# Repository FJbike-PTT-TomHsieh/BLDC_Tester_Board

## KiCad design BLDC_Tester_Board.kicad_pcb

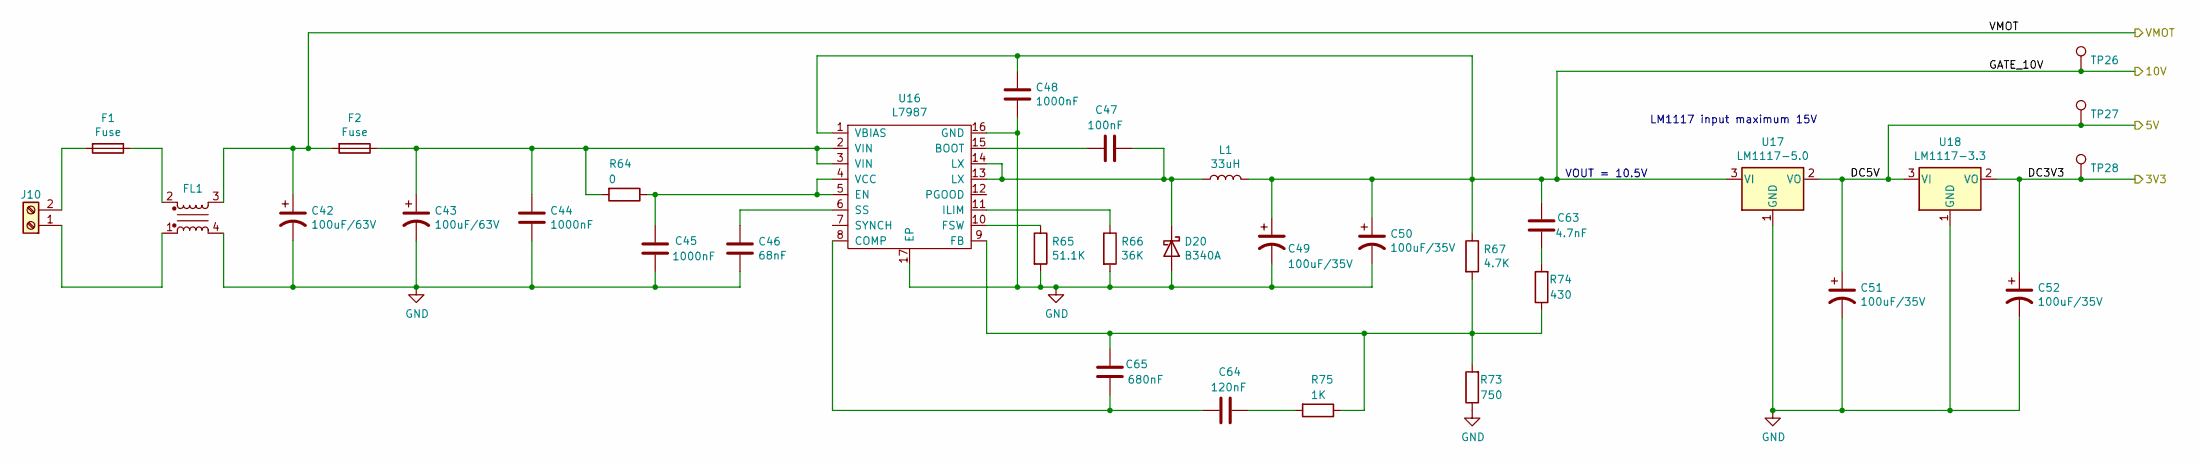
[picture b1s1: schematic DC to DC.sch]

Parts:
C42, C43: 100uF/63V; CP_Radial_D12.5mm_P5.00mm
C44, C45, C48: 1000nF; C_0603_1608Metric_Pad1.08x0.95mm_HandSolder
C46: 68nF; C_0603_1608Metric_Pad1.08x0.95mm_HandSolder
C47: 100nF; C_0603_1608Metric_Pad1.08x0.95mm_HandSolder
C49, C50, C51, C52: 100uF/35V; CP_Radial_D8.0mm_P3.50mm
C63: 4.7nF; C_0603_1608Metric_Pad1.08x0.95mm_HandSolder
C64: 120nF; C_0603_1608Metric_Pad1.08x0.95mm_HandSolder
C65: 680nF; C_0603_1608Metric_Pad1.08x0.95mm_HandSolder
D20: B340A; D_SMA_Handsoldering
F1: Fuse; Fuseholder_Cylinder-5x20mm_Stelvio-Kontek_PTF78_Horizontal_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
F2: Fuse; Fuse_1206_3216Metric_Pad1.42x1.75mm_HandSolder
FL1: EMI_Filter_LL_1423; Choke_Schaffner_RN242-04-18.0x31.0mm
J10: Screw_Terminal_01x02; TerminalBlock_Altech_AK300-2_P5.00mm
L1: 33uH; L_7.3x7.3_H4.5
R64: 0; R_0603_1608Metric_Pad0.98x0.95mm_HandSolder
R65: 51.1K; R_0603_1608Metric_Pad0.98x0.95mm_HandSolder
R66: 36K; R_0603_1608Metric_Pad0.98x0.95mm_HandSolder
R67: 4.7K; R_0603_1608Metric_Pad0.98x0.95mm_HandSolder
R73: 750; R_0603_1608Metric_Pad0.98x0.95mm_HandSolder
R74: 430; R_0603_1608Metric_Pad0.98x0.95mm_HandSolder
R75: 1K; R_0603_1608Metric_Pad0.98x0.95mm_HandSolder
TP26, TP27, TP28: TestPoint; TestPoint_Loop_D2.54mm_Drill1.5mm_Beaded
U16: L7987; HTSSOP-16-1EP_4.4x5mm_P0.65mm_EP3x3mm
U17: LM1117-5.0; SOT-223-3_TabPin2
U18: LM1117-3.3; SOT-223-3_TabPin2

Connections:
/DC to DC/3V3: C52.1, TP28.1, U18.2 (VO); also elsewhere on the board
/DC to DC/5V: C51.1, TP27.1, U17.2 (VO), U18.3 (VI); also elsewhere on the board
/DC to DC/10V: C48.1, C49.1, C50.1, C63.2, L1.2, R67.1, TP26.1, U16.1 (VBIAS), U17.3 (VI); also elsewhere on the board
/DC to DC/VMOT: C42.1, F2.2, FL1.3; also elsewhere on the board
GND: C42.2, C43.2, C44.2, C45.1, C46.2, C48.2, C49.2, C50.2, C51.2, C52.2, D20.2 (A), FL1.4, R65.2, R66.2, R73.1, U16.16 (GND), U16.17 (EP), U17.1 (GND), U18.1 (GND); also elsewhere on the board
unnamed: C43.1, C44.1, F2.1, R64.2, U16.2 (VIN), U16.3 (VIN)
unnamed: C45.2, R64.1, U16.4 (VCC), U16.5 (EN)
unnamed: C46.1, U16.6 (SS)
unnamed: C47.1, D20.1 (K), L1.1, U16.13 (LX), U16.14 (LX)
unnamed: C47.2, U16.15 (BOOT)
unnamed: C63.1, R74.2
unnamed: C64.1, R75.2
unnamed: C64.2, C65.1, U16.8 (COMP)
unnamed: C65.2, R67.2, R73.2, R74.1, R75.1, U16.9 (FB)
unnamed: F1.1, FL1.2
unnamed: F1.2, J10.2
unnamed: FL1.1, J10.1
unnamed: R65.1, U16.10 (FSW)
unnamed: R66.1, U16.11 (ILIM)

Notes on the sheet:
VOUT = 10.5V
LM1117 input maximum 15V

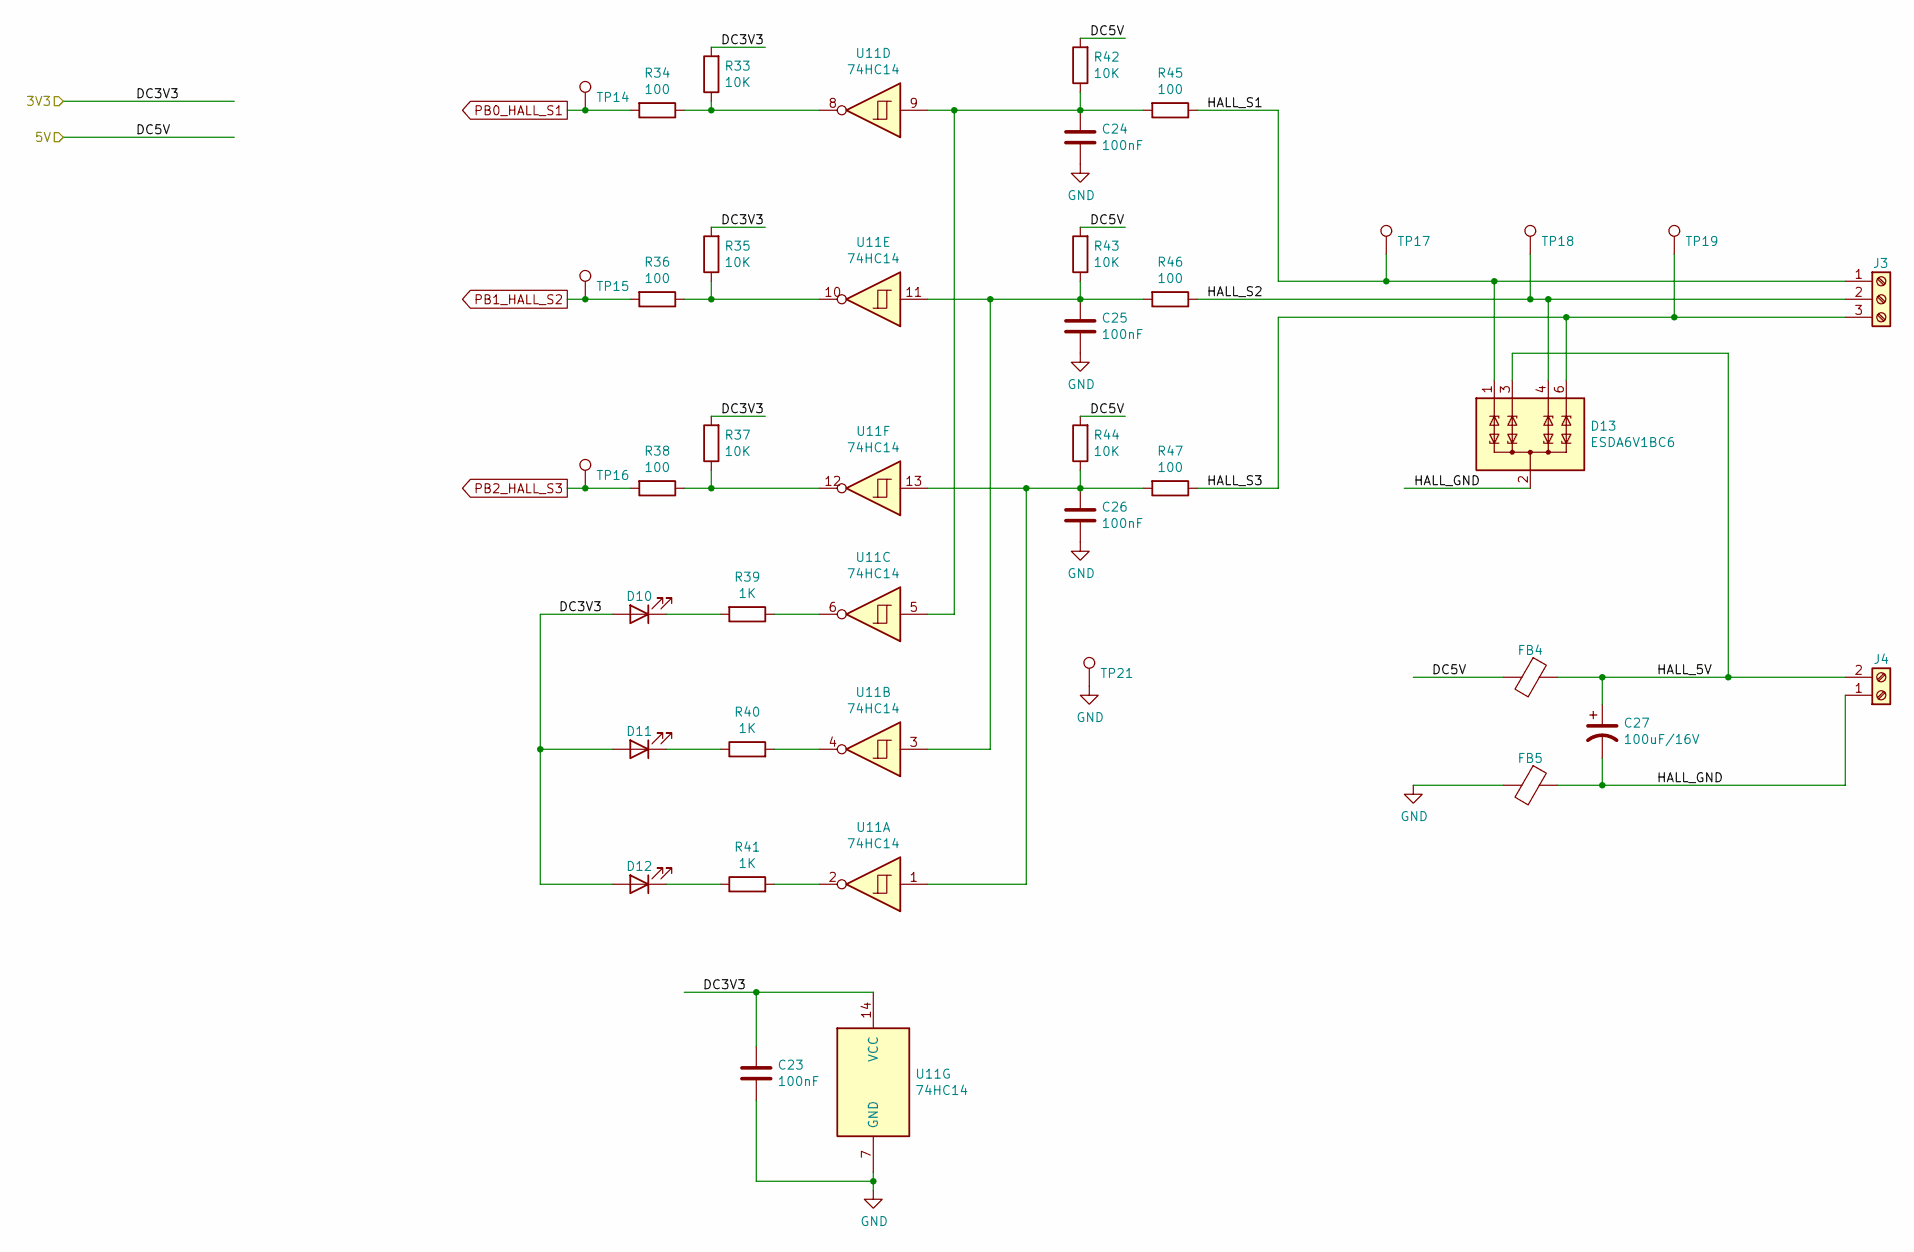
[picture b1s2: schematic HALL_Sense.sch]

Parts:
C23, C24, C25, C26: 100nF; C_0603_1608Metric_Pad1.08x0.95mm_HandSolder
C27: 100uF/16V; CP_Radial_D8.0mm_P3.50mm
D10: PESD5V0L4UG; LED_D3.0mm
D11, D12: LED; LED_D3.0mm
D13: ESDA6V1BC6; SOT-23-6_Handsoldering
FB4, FB5: Ferrite_Bead; R_0603_1608Metric_Pad0.98x0.95mm_HandSolder
J3: Screw_Terminal_01x03; TerminalBlock_4Ucon_1x03_P3.50mm_Horizontal
J4: Screw_Terminal_01x02; TerminalBlock_4Ucon_1x02_P3.50mm_Horizontal
R33, R35, R37, R42, R43, R44: 10K; R_0603_1608Metric_Pad0.98x0.95mm_HandSolder
R34, R36, R38, R45, R46, R47: 100; R_0603_1608Metric_Pad0.98x0.95mm_HandSolder
R39, R40, R41: 1K; R_0603_1608Metric_Pad0.98x0.95mm_HandSolder
TP14, TP15, TP16, TP17, TP18, TP19, TP21: TestPoint; TestPoint_Loop_D2.54mm_Drill1.5mm_Beaded
U11: 74HC14; SO-14_3.9x8.65mm_P1.27mm

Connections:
/DC to DC/3V3: C23.1, D10.2 (A), D11.2 (A), D12.2 (A), R33.2, R35.2, R37.2, U11.14 (VCC); also elsewhere on the board
/DC to DC/5V: FB4.2, R42.2, R43.2, R44.2; also elsewhere on the board
/HALL_Sense/HALL_5V: C27.1, D13.3 (TVS2), FB4.1, J4.2
/HALL_Sense/HALL_GND: C27.2, D13.2 (COM), D13.5 (COM), FB5.1, J4.1
/HALL_Sense/HALL_S1: D13.1 (TVS1), J3.1, R45.1, TP17.1
/HALL_Sense/HALL_S2: D13.4 (TVS3), J3.2, R46.1, TP18.1
/HALL_Sense/HALL_S3: D13.6 (TVS4), J3.3, R47.1, TP19.1
GND: C23.2, C24.2, C25.2, C26.2, FB5.2, TP21.1, U11.7 (GND); also elsewhere on the board
unnamed: C24.1, R42.1, R45.2, U11.5, U11.9
unnamed: C25.1, R43.1, R46.2, U11.3, U11.11
unnamed: C26.1, R44.1, R47.2, U11.1, U11.13
unnamed: D10.1 (K), R39.2
unnamed: D11.1 (K), R40.1
unnamed: D12.1 (K), R41.1
unnamed: R33.1, R34.1, U11.8
unnamed: R35.1, R36.1, U11.10
unnamed: R37.1, R38.1, U11.12
unnamed: R39.1, U11.6
unnamed: R40.2, U11.4
unnamed: R41.2, U11.2
PB0_HALL_S1: R34.2, TP14.1; also elsewhere on the board
PB1_HALL_S2: R36.2, TP15.1; also elsewhere on the board
PB2_HALL_S3: R38.2, TP16.1; also elsewhere on the board

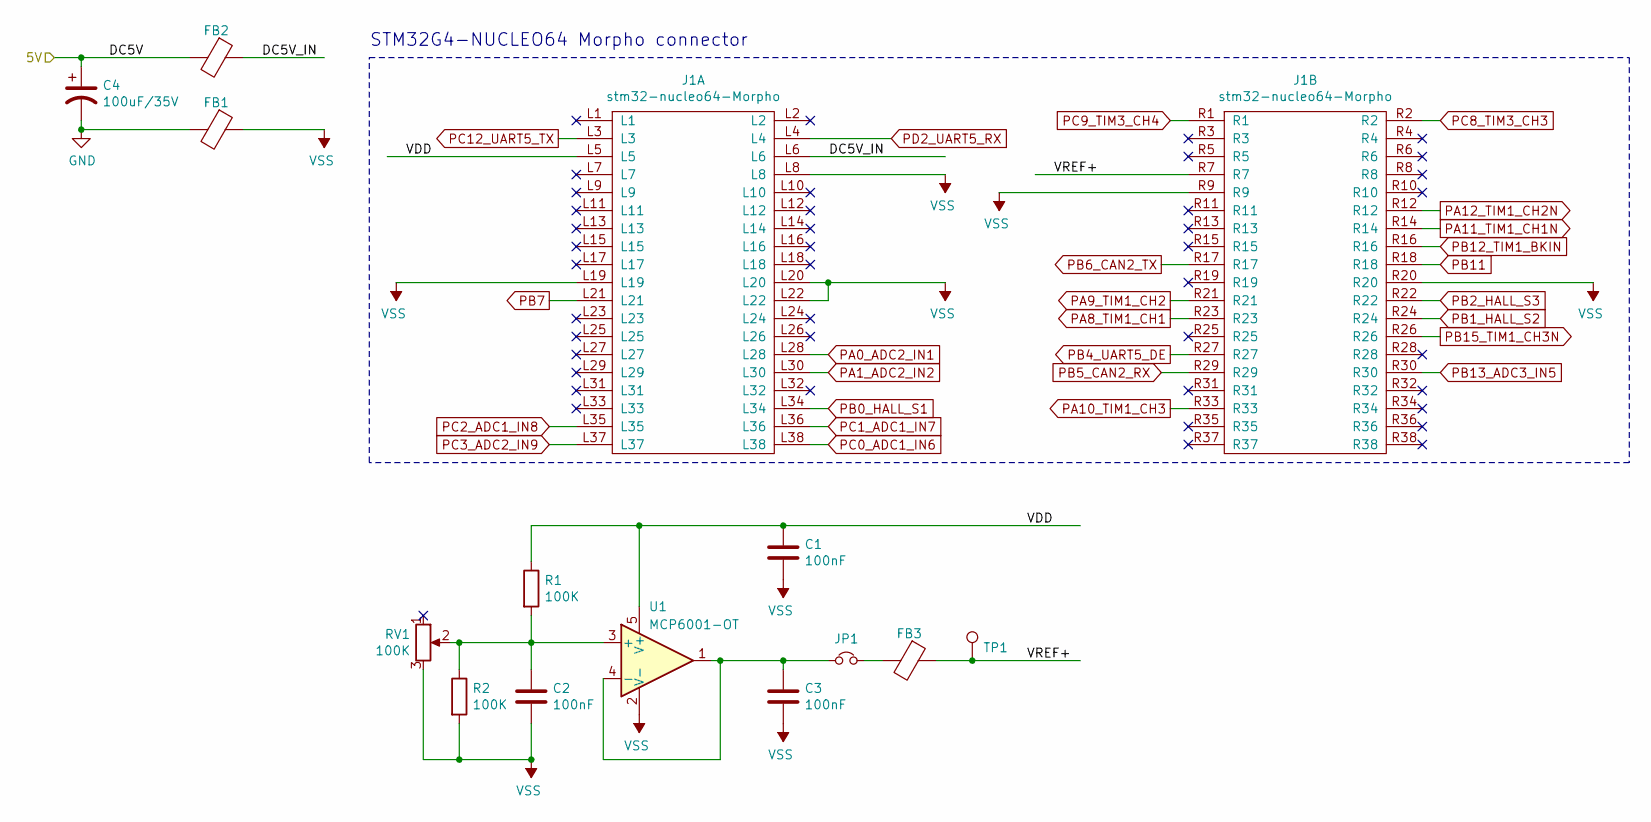
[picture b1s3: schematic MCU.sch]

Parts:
C1, C2, C3: 100nF; C_0603_1608Metric_Pad1.08x0.95mm_HandSolder
C4: 100uF/35V; CP_Radial_D6.3mm_P2.50mm
FB1, FB2, FB3: Ferrite_Bead; R_0603_1608Metric_Pad0.98x0.95mm_HandSolder
J1: stm32-nucleo64-Morpho
JP1: Jumper_NC_Small; PinHeader_1x02_P2.54mm_Vertical
R1, R2: 100K; R_0603_1608Metric_Pad0.98x0.95mm_HandSolder
RV1: 100K; Potentiometer_Bourns_3386F_Vertical
TP1: TestPoint; TestPoint_Loop_D2.54mm_Drill1.5mm_Beaded
U1: MCP6001-OT; SOT-23-5_HandSoldering

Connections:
/DC to DC/5V: C4.1, FB2.2; also elsewhere on the board
/MCU/DC5V_IN: FB2.1, J1.L6
/MCU/VDD: C1.1, J1.L5, R1.1, U1.5 (V+)
/MCU/VREF+: FB3.1, J1.R7, TP1.1
GND: C4.2, FB1.2; also elsewhere on the board
unnamed: C2.1, R1.2, R2.1, RV1.2, U1.3 (+)
unnamed: C3.1, JP1.1, U1.1, U1.4 (-)
unnamed: FB3.2, JP1.2
PA0_ADC2_IN1: J1.L28; also elsewhere on the board
PA1_ADC2_IN2: J1.L30; also elsewhere on the board
PA8_TIM1_CH1: J1.R23; also elsewhere on the board
PA9_TIM1_CH2: J1.R21; also elsewhere on the board
PA10_TIM1_CH3: J1.R33; also elsewhere on the board
PA11_TIM1_CH1N: J1.R14; also elsewhere on the board
PA12_TIM1_CH2N: J1.R12; also elsewhere on the board
PB0_HALL_S1: J1.L34; also elsewhere on the board
PB1_HALL_S2: J1.R24; also elsewhere on the board
PB2_HALL_S3: J1.R22; also elsewhere on the board
PB4_UART5_DE: J1.R27; also elsewhere on the board
PB5_CAN2_RX: J1.R29; also elsewhere on the board
PB6_CAN2_TX: J1.R17; also elsewhere on the board
PB7: J1.L21; also elsewhere on the board
PB11: J1.R18; also elsewhere on the board
PB12_TIM1_BKIN: J1.R16; also elsewhere on the board
PB13_ADC3_IN5: J1.R30; also elsewhere on the board
PB15_TIM1_CH3N: J1.R26; also elsewhere on the board
PC0_ADC1_IN6: J1.L38; also elsewhere on the board
PC1_ADC1_IN7: J1.L36; also elsewhere on the board
PC2_ADC1_IN8: J1.L35; also elsewhere on the board
PC3_ADC2_IN9: J1.L37; also elsewhere on the board
PC8_TIM3_CH3: J1.R2; also elsewhere on the board
PC9_TIM3_CH4: J1.R1; also elsewhere on the board
PC12_UART5_TX: J1.L3; also elsewhere on the board
PD2_UART5_RX: J1.L4; also elsewhere on the board
VSS: C1.2, C2.2, C3.2, FB1.1, J1.L8, J1.L19, J1.L20, J1.L22, J1.R9, J1.R20, R2.2, RV1.3, U1.2 (V-)

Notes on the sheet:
STM32G4-NUCLEO64 Morpho connector

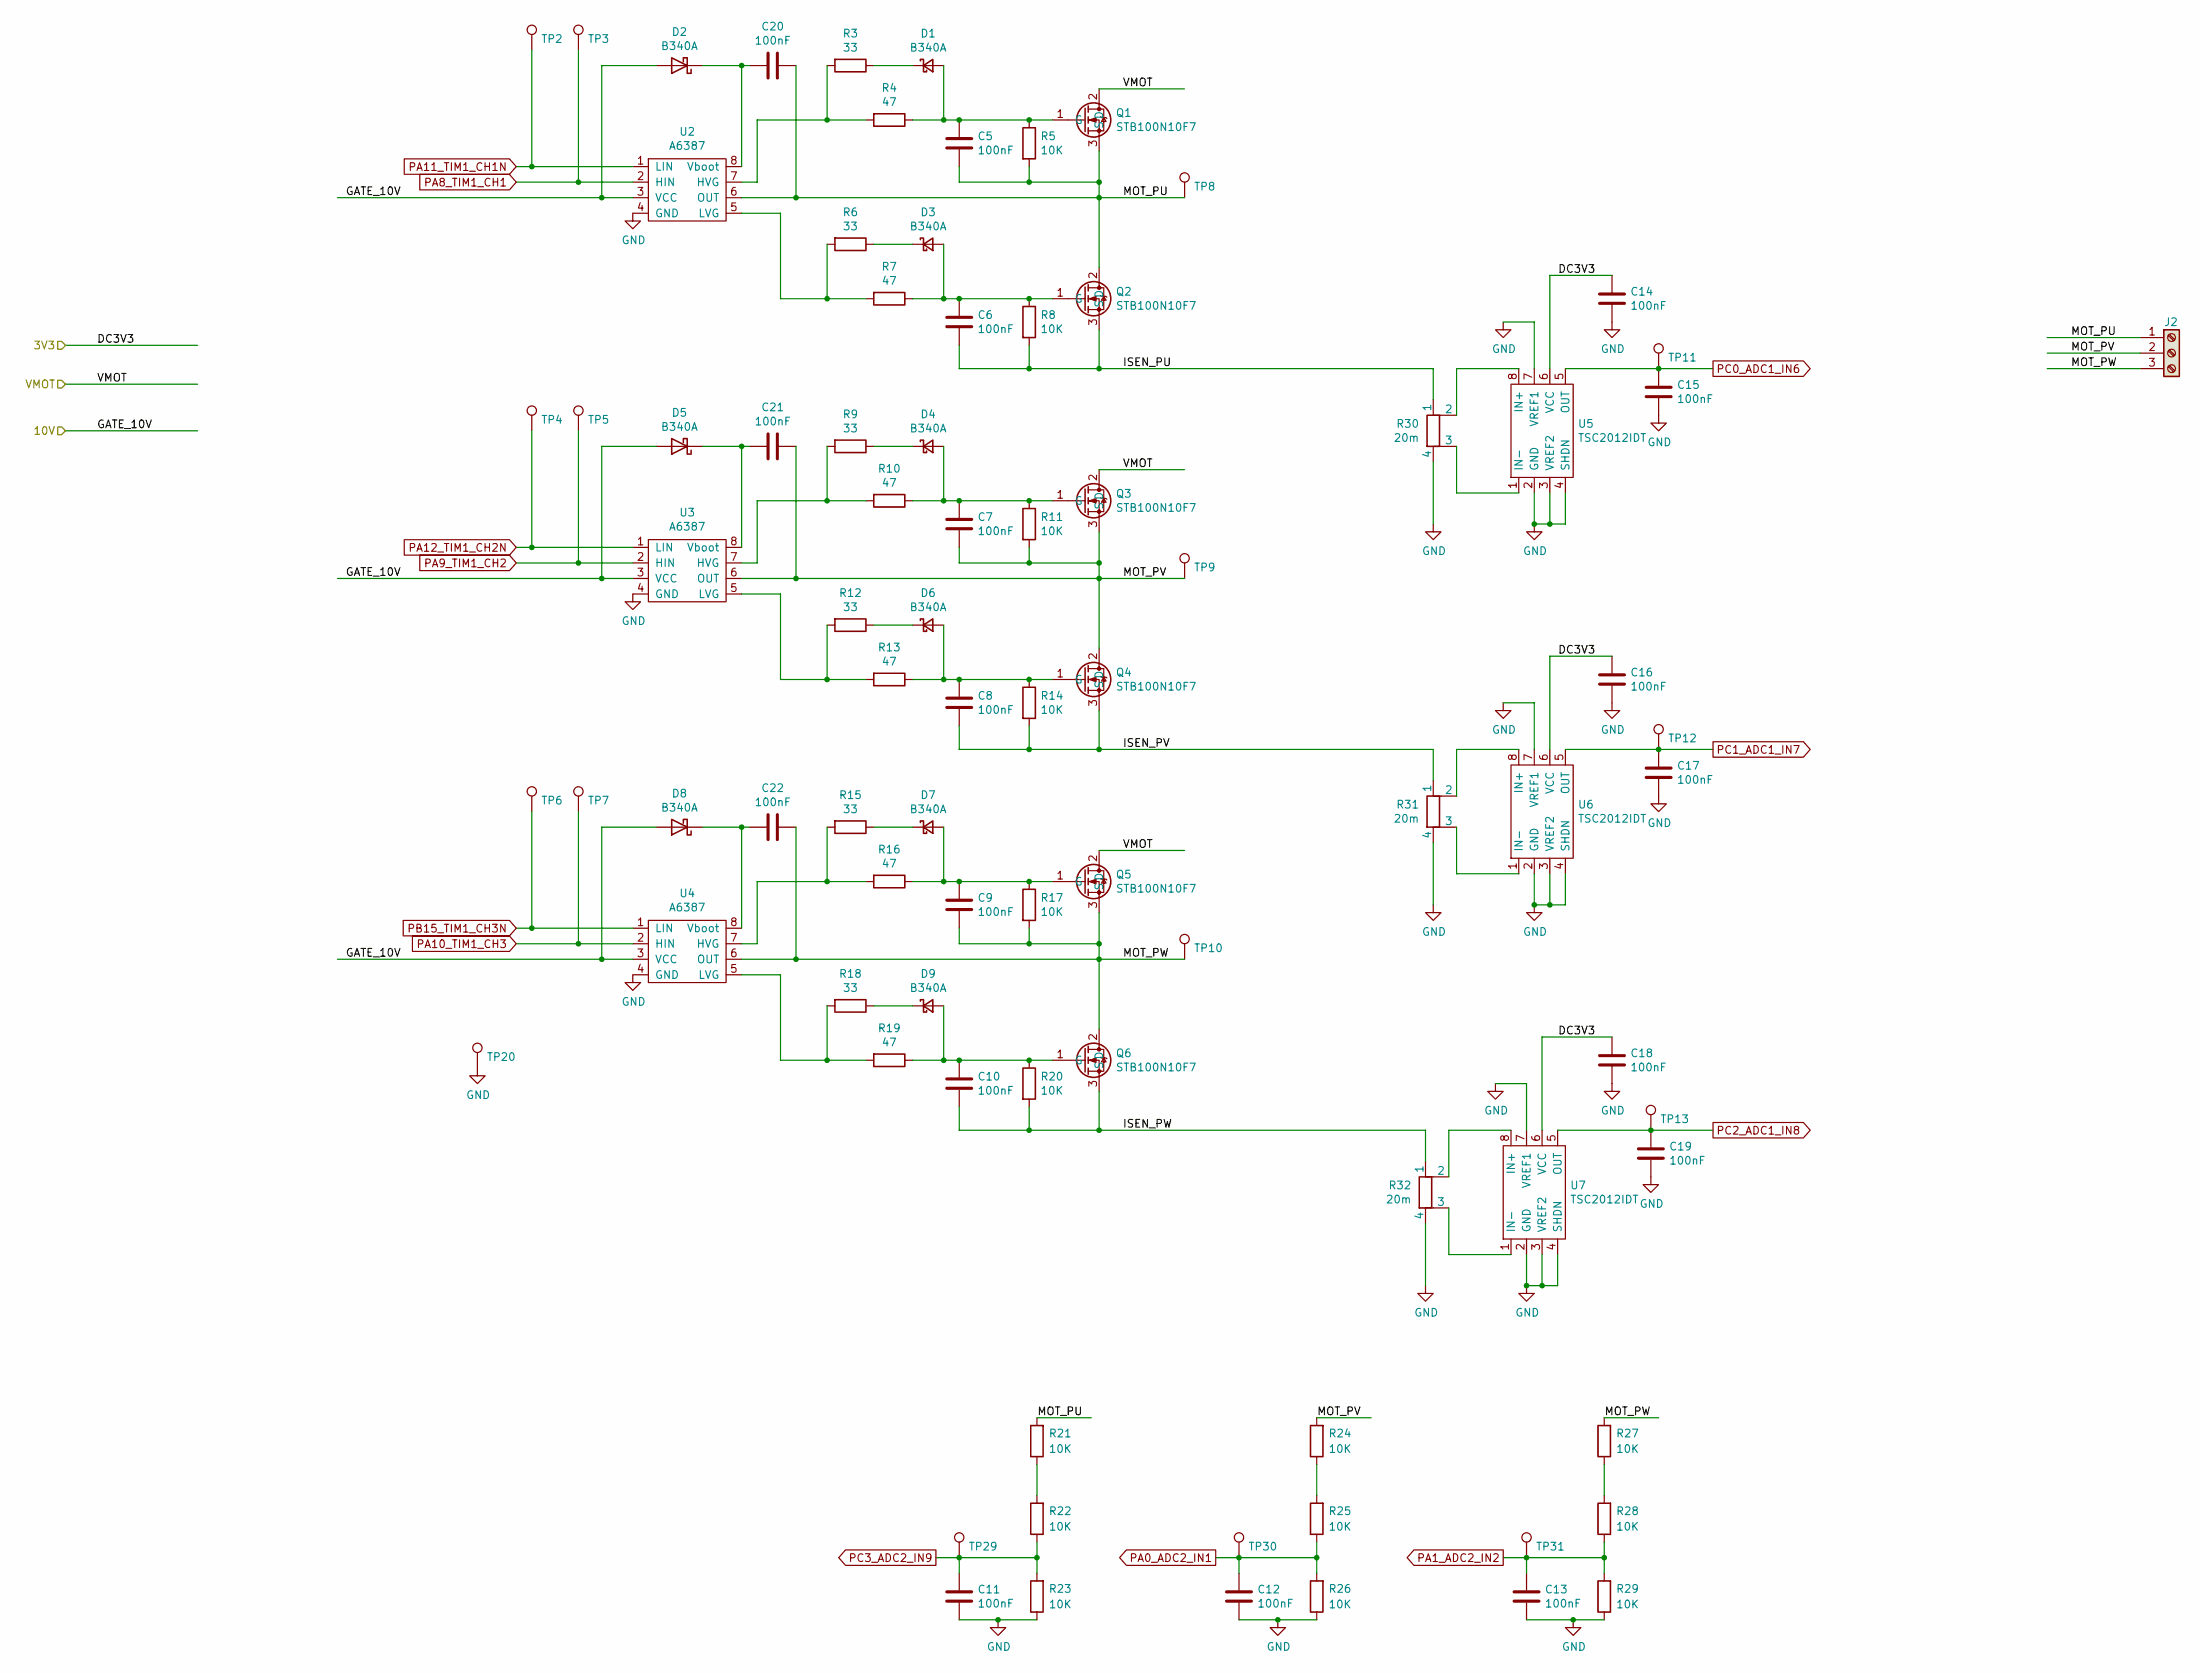
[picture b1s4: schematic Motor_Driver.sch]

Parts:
C5, C6, C7, C8, C9, C10, C11, C12, C13, C14, C15, C16, C17, C18, C19, C20, C21, C22: 100nF; C_0603_1608Metric_Pad1.08x0.95mm_HandSolder
D1, D2, D3, D4, D5, D6, D7, D8, D9: B340A; D_SMA_Handsoldering
J2: Screw_Terminal_01x03; TerminalBlock_Altech_AK300-3_P5.00mm
Q1, Q2, Q3, Q4, Q5, Q6: STB100N10F7; TO-263-2
R3, R6, R9, R12, R15, R18: 33; R_0603_1608Metric_Pad0.98x0.95mm_HandSolder
R4, R7, R10, R16, R19: 47; R_0603_1608Metric_Pad0.98x0.95mm_HandSolder
R5, R8, R11, R14, R17, R20: 10K; R_0603_1608Metric_Pad0.98x0.95mm_HandSolder
R13: 47; R_0603_1608Metric
R21, R22, R23, R24, R25, R26, R27, R28, R29: 10K; R_1206_3216Metric_Pad1.30x1.75mm_HandSolder
R30, R31, R32: 20m; R_Shunt_Vishay_WSKW0612
TP2, TP3, TP4, TP5, TP6, TP7, TP8, TP9, TP10, TP11, TP12, TP13, TP20, TP29, TP30, TP31: TestPoint; TestPoint_Loop_D2.54mm_Drill1.5mm_Beaded
U2, U3, U4: A6387; SO-8_3.9x4.9mm_P1.27mm
U5, U6, U7: TSC2012IDT; SO-8_3.9x4.9mm_P1.27mm

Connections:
/DC to DC/3V3: C14.1, C16.1, C18.1, U5.6 (VCC), U6.6 (VCC), U7.6 (VCC); also elsewhere on the board
/DC to DC/10V: D2.2 (A), D5.2 (A), D8.2 (A), U2.3 (VCC), U3.3 (VCC), U4.3 (VCC); also elsewhere on the board
/DC to DC/VMOT: Q1.2 (D), Q3.2 (D), Q5.2 (D); also elsewhere on the board
/MotorDriver/ISEN_PU: C6.2, Q2.3 (S), R8.2, R30.1
/MotorDriver/ISEN_PV: C8.2, Q4.3 (S), R14.2, R31.1
/MotorDriver/ISEN_PW: C10.2, Q6.3 (S), R20.2, R32.1
/MotorDriver/MOT_PU: C5.2, C20.1, J2.1, Q1.3 (S), Q2.2 (D), R5.2, R21.2, TP8.1, U2.6 (OUT)
/MotorDriver/MOT_PV: C7.2, C21.1, J2.2, Q3.3 (S), Q4.2 (D), R11.2, R24.2, TP9.1, U3.6 (OUT)
/MotorDriver/MOT_PW: C9.2, C22.1, J2.3, Q5.3 (S), Q6.2 (D), R17.2, R27.2, TP10.1, U4.6 (OUT)
GND: C11.2, C12.2, C13.2, C14.2, C15.2, C16.2, C17.2, C18.2, C19.2, R23.1, R26.1, R29.1, R30.4, R31.4, R32.4, TP20.1, U2.4 (GND), U3.4 (GND), U4.4 (GND), U5.2 (GND), U5.3 (VREF2), U5.4 (SHDN), U5.7 (VREF1), U6.2 (GND), U6.3 (VREF2), U6.4 (SHDN), U6.7 (VREF1), U7.2 (GND), U7.3 (VREF2), U7.4 (SHDN), U7.7 (VREF1); also elsewhere on the board
unnamed: C5.1, D1.2 (A), Q1.1 (G), R4.1, R5.1
unnamed: C6.1, D3.2 (A), Q2.1 (G), R7.1, R8.1
unnamed: C7.1, D4.2 (A), Q3.1 (G), R10.1, R11.1
unnamed: C8.1, D6.2 (A), Q4.1 (G), R13.1, R14.1
unnamed: C9.1, D7.2 (A), Q5.1 (G), R16.1, R17.1
unnamed: C10.1, D9.2 (A), Q6.1 (G), R19.1, R20.1
unnamed: C20.2, D2.1 (K), U2.8 (Vboot)
unnamed: C21.2, D5.1 (K), U3.8 (Vboot)
unnamed: C22.2, D8.1 (K), U4.8 (Vboot)
unnamed: D1.1 (K), R3.1
unnamed: D3.1 (K), R6.1
unnamed: D4.1 (K), R9.1
unnamed: D6.1 (K), R12.1
unnamed: D7.1 (K), R15.1
unnamed: D9.1 (K), R18.1
unnamed: R3.2, R4.2, U2.7 (HVG)
unnamed: R6.2, R7.2, U2.5 (LVG)
unnamed: R9.2, R10.2, U3.7 (HVG)
unnamed: R12.2, R13.2, U3.5 (LVG)
unnamed: R15.2, R16.2, U4.7 (HVG)
unnamed: R18.2, R19.2, U4.5 (LVG)
unnamed: R21.1, R22.2
unnamed: R24.1, R25.2
unnamed: R27.1, R28.2
unnamed: R30.2, U5.8 (IN+)
unnamed: R30.3, U5.1 (IN-)
unnamed: R31.2, U6.8 (IN+)
unnamed: R31.3, U6.1 (IN-)
unnamed: R32.2, U7.8 (IN+)
unnamed: R32.3, U7.1 (IN-)
PA0_ADC2_IN1: C12.1, R25.1, R26.2, TP30.1; also elsewhere on the board
PA1_ADC2_IN2: C13.1, R28.1, R29.2, TP31.1; also elsewhere on the board
PA8_TIM1_CH1: TP3.1, U2.2 (HIN); also elsewhere on the board
PA9_TIM1_CH2: TP5.1, U3.2 (HIN); also elsewhere on the board
PA10_TIM1_CH3: TP7.1, U4.2 (HIN); also elsewhere on the board
PA11_TIM1_CH1N: TP2.1, U2.1 (LIN); also elsewhere on the board
PA12_TIM1_CH2N: TP4.1, U3.1 (LIN); also elsewhere on the board
PB15_TIM1_CH3N: TP6.1, U4.1 (LIN); also elsewhere on the board
PC0_ADC1_IN6: C15.1, TP11.1, U5.5 (OUT); also elsewhere on the board
PC1_ADC1_IN7: C17.1, TP12.1, U6.5 (OUT); also elsewhere on the board
PC2_ADC1_IN8: C19.1, TP13.1, U7.5 (OUT); also elsewhere on the board
PC3_ADC2_IN9: C11.1, R22.1, R23.2, TP29.1; also elsewhere on the board

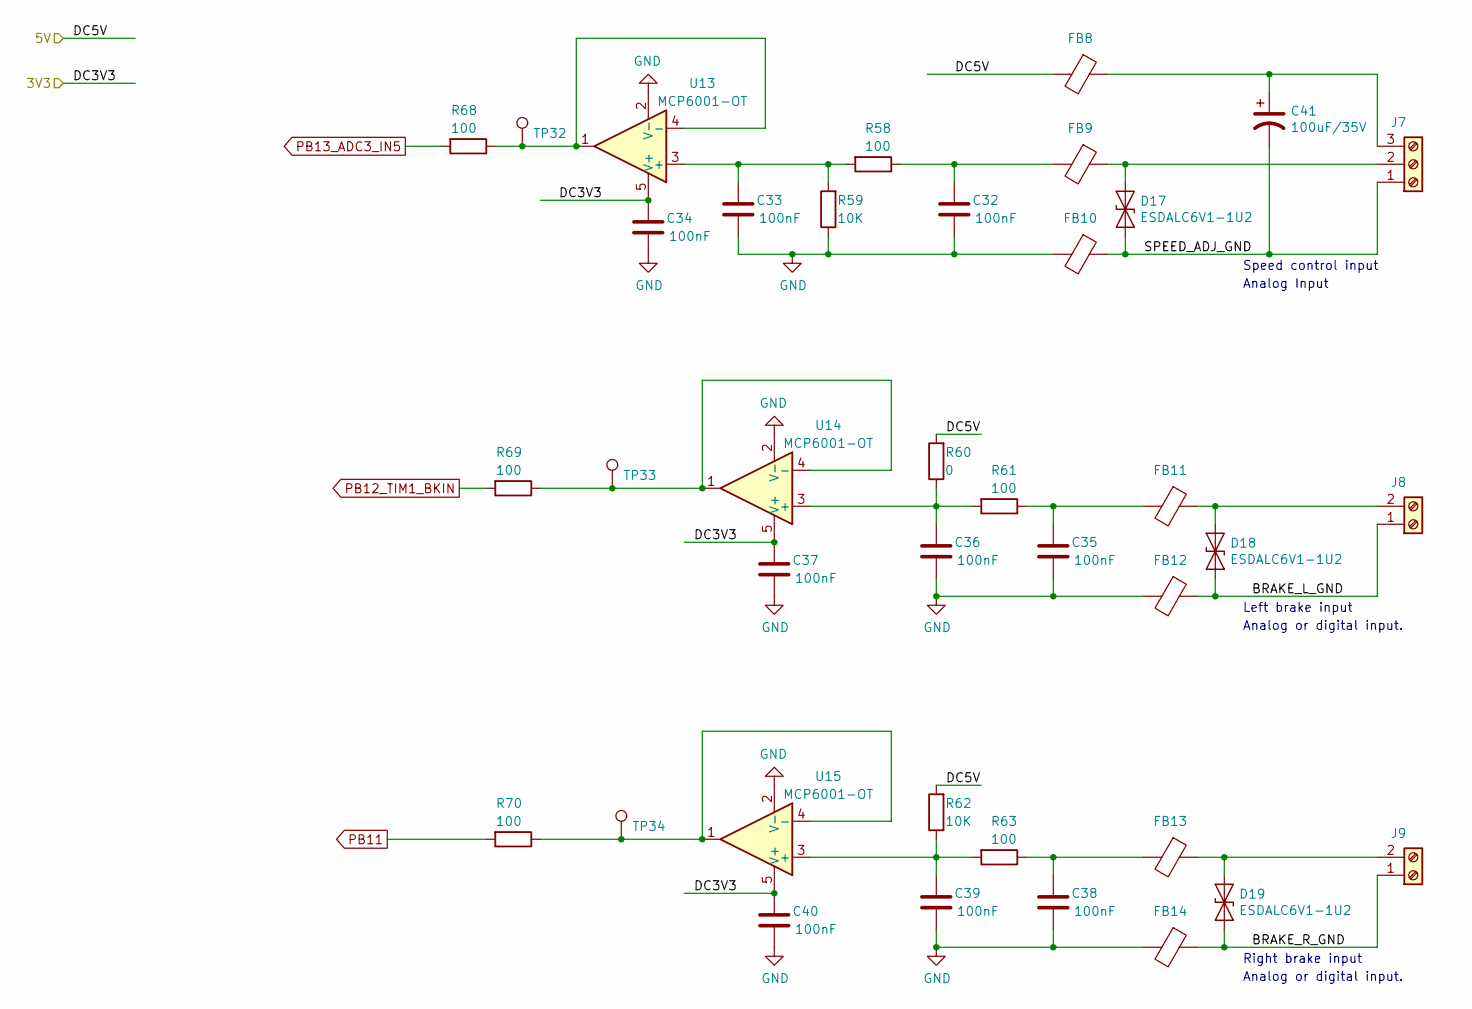
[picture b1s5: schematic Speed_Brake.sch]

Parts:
C32, C33, C34, C35, C36, C37, C38, C39, C40: 100nF; C_0603_1608Metric_Pad1.08x0.95mm_HandSolder
C41: 100uF/35V; CP_Radial_D8.0mm_P3.50mm
D17, D18, D19: ESDALC6V1-1U2; D_0805_2012Metric_Pad1.15x1.40mm_HandSolder
FB8, FB9, FB10, FB11, FB12, FB13, FB14: Ferrite_Bead; R_0603_1608Metric_Pad0.98x0.95mm_HandSolder
J7: Screw_Terminal_01x03; TerminalBlock_4Ucon_1x03_P3.50mm_Horizontal
J8, J9: Screw_Terminal_01x02; TerminalBlock_4Ucon_1x02_P3.50mm_Horizontal
R58, R61, R63, R68, R69, R70: 100; R_0603_1608Metric_Pad0.98x0.95mm_HandSolder
R59, R62: 10K; R_0603_1608Metric_Pad0.98x0.95mm_HandSolder
R60: 0; R_0603_1608Metric_Pad0.98x0.95mm_HandSolder
TP32, TP33, TP34: TestPoint; TestPoint_Loop_D2.54mm_Drill1.5mm_Beaded
U13, U14, U15: MCP6001-OT; SOT-23-5_HandSoldering

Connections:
/DC to DC/3V3: C34.2, C37.2, C40.2, U13.5 (V+), U14.5 (V+), U15.5 (V+); also elsewhere on the board
/DC to DC/5V: FB8.2, R60.2, R62.2; also elsewhere on the board
/Speed control and Brake/BRAKE_L_GND: D18.2 (A2), FB12.1, J8.1
/Speed control and Brake/BRAKE_R_GND: D19.2 (A2), FB14.1, J9.1
/Speed control and Brake/SPEED_ADJ_GND: C41.2, D17.2 (A2), FB10.1, J7.1
GND: C32.1, C33.1, C34.1, C35.1, C36.1, C37.1, C38.1, C39.1, C40.1, FB10.2, FB12.2, FB14.2, R59.1, U13.2 (V-), U14.2 (V-), U15.2 (V-); also elsewhere on the board
unnamed: C32.2, FB9.2, R58.1
unnamed: C33.2, R58.2, R59.2, U13.3 (+)
unnamed: C35.2, FB11.2, R61.1
unnamed: C36.2, R60.1, R61.2, U14.3 (+)
unnamed: C38.2, FB13.2, R63.1
unnamed: C39.2, R62.1, R63.2, U15.3 (+)
unnamed: C41.1, FB8.1, J7.3
unnamed: D17.1 (A1), FB9.1, J7.2
unnamed: D18.1 (A1), FB11.1, J8.2
unnamed: D19.1 (A1), FB13.1, J9.2
unnamed: R68.1, TP32.1, U13.1, U13.4 (-)
unnamed: R69.1, TP33.1, U14.1, U14.4 (-)
unnamed: R70.1, TP34.1, U15.1, U15.4 (-)
PB11: R70.2; also elsewhere on the board
PB12_TIM1_BKIN: R69.2; also elsewhere on the board
PB13_ADC3_IN5: R68.2; also elsewhere on the board

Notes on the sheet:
Speed control input
Left brake input
Right brake input
Analog Input
Analog or digital input.

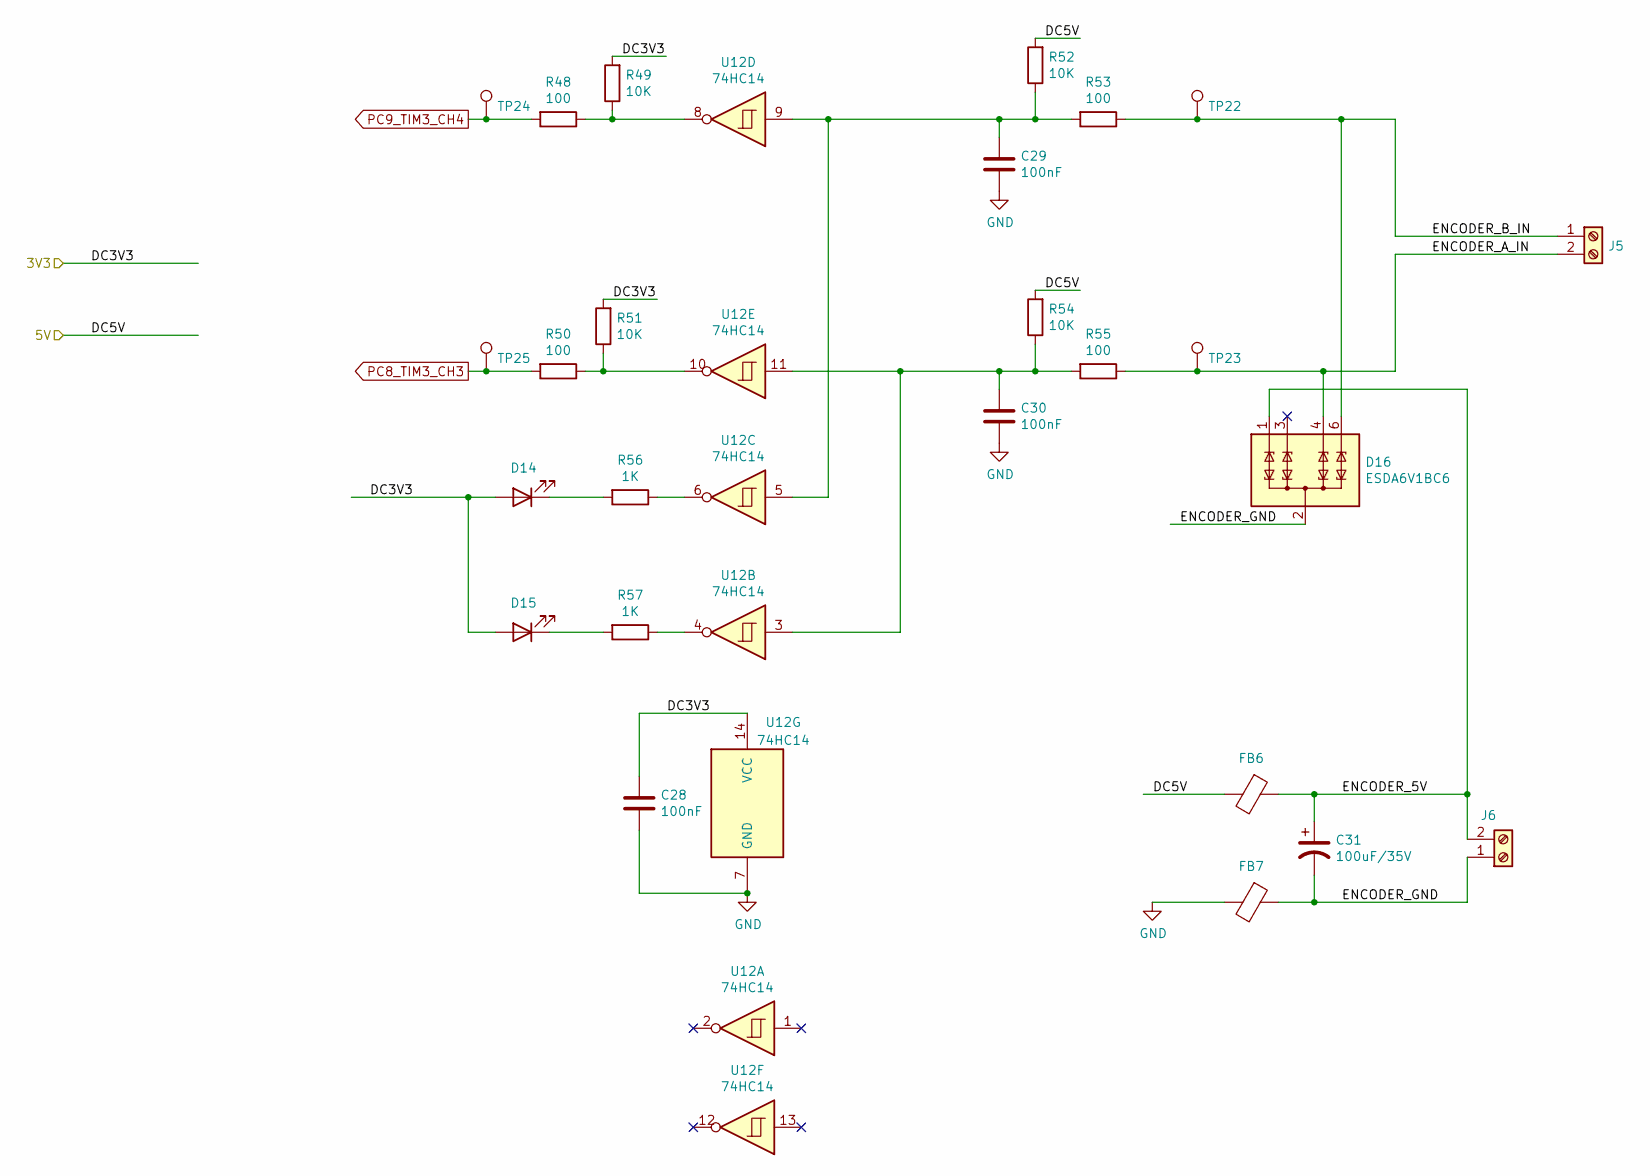
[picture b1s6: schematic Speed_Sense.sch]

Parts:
C28, C29, C30: 100nF; C_0603_1608Metric_Pad1.08x0.95mm_HandSolder
C31: 100uF/35V; CP_Radial_D8.0mm_P3.50mm
D14, D15: LED; LED_D3.0mm
D16: ESDA6V1BC6; SOT-23-6_Handsoldering
FB6, FB7: Ferrite_Bead; R_0603_1608Metric_Pad0.98x0.95mm_HandSolder
J5, J6: Screw_Terminal_01x02; TerminalBlock_4Ucon_1x02_P3.50mm_Horizontal
R48, R50, R53, R55: 100; R_0603_1608Metric_Pad0.98x0.95mm_HandSolder
R49, R51, R52, R54: 10K; R_0603_1608Metric_Pad0.98x0.95mm_HandSolder
R56, R57: 1K; R_0603_1608Metric_Pad0.98x0.95mm_HandSolder
TP22, TP23, TP24, TP25: TestPoint; TestPoint_Loop_D2.54mm_Drill1.5mm_Beaded
U12: 74HC14; SO-14_3.9x8.65mm_P1.27mm

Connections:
/DC to DC/3V3: C28.1, D14.2 (A), D15.2 (A), R49.2, R51.2, U12.14 (VCC); also elsewhere on the board
/DC to DC/5V: FB6.2, R52.2, R54.2; also elsewhere on the board
/Speed_Sense/ENCODER_5V: C31.1, D16.1 (TVS1), FB6.1, J6.2
/Speed_Sense/ENCODER_A_IN: D16.4 (TVS3), J5.2, R55.1, TP23.1
/Speed_Sense/ENCODER_B_IN: D16.6 (TVS4), J5.1, R53.1, TP22.1
/Speed_Sense/ENCODER_GND: C31.2, D16.2 (COM), D16.5 (COM), FB7.1, J6.1
GND: C28.2, C29.2, C30.2, FB7.2, U12.7 (GND); also elsewhere on the board
unnamed: C29.1, R52.1, R53.2, U12.5, U12.9
unnamed: C30.1, R54.1, R55.2, U12.3, U12.11
unnamed: D14.1 (K), R56.2
unnamed: D15.1 (K), R57.2
unnamed: R48.1, R49.1, U12.8
unnamed: R50.1, R51.1, U12.10
unnamed: R56.1, U12.6
unnamed: R57.1, U12.4
PC8_TIM3_CH3: R50.2, TP25.1; also elsewhere on the board
PC9_TIM3_CH4: R48.2, TP24.1; also elsewhere on the board
